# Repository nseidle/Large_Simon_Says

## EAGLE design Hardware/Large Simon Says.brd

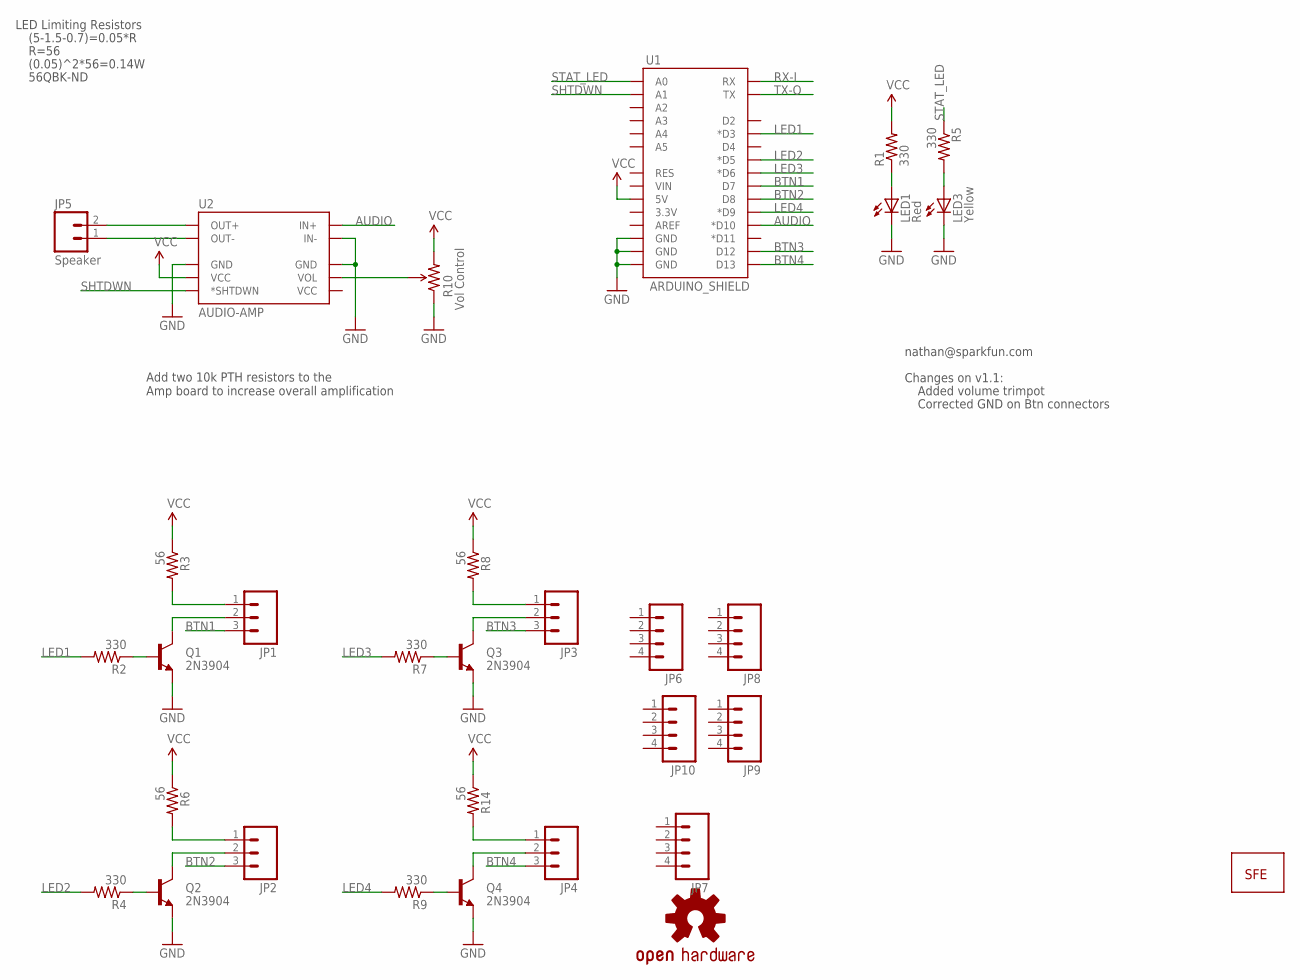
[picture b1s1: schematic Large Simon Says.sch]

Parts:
JP1, JP2, JP3, JP4: M03JST-PTH-VERT; JST-3-PTH-VERT
JP5: Speaker; JST-2-PTH
JP6, JP7, JP8, JP9, JP10: M04JST-PTH; JST-4-PTH
LED1: Red; LED5MM
LED3: Yellow; LED5MM
Q1, Q2, Q3, Q4: 2N3904; TO-92
R1, R2, R4, R5, R7, R9: 330; AXIAL-0.3
R3, R6, R8, R14: 56; AXIAL-0.3
R10: Vol Control; 3386U
U1: ARDUINO_SHIELD; DUEMILANOVE_SHIELD_NOHOLES
U2: AUDIO-AMP; AUDIO-AMP-MONO
U$1: LOGO-SFENEW; SFE-NEW-WEBLOGO
U$3: OSHW-LOGOS; OSHW-LOGO-S

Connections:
AUDIO: U1.D10 (*D10), U2.IN+
BTN1: JP1.3, U1.D7
BTN2: JP2.3, U1.D8
BTN3: JP3.3, U1.D12
BTN4: JP4.3, U1.D13
GND: LED1.K (C), LED3.K (C), Q1.1 (E), Q2.1 (E), Q3.1 (E), Q4.1 (E), R10.1 (CCW), U1.GND@0 (GND), U1.GND@1 (GND), U1.GND@2 (GND), U2.IN-, U2.PWR- (GND), U2.VOL- (GND)
LED1: R2.P$2 (2), U1.D3 (*D3)
LED2: R4.P$2 (2), U1.D5 (*D5)
LED3: R7.P$2 (2), U1.D6 (*D6)
LED4: R9.P$2 (2), U1.D9 (*D9)
unnamed: LED1.A, R1.P$1 (1)
unnamed: Q1.2 (B), R2.P$1 (1)
unnamed: JP1.2, Q1.3 (C)
unnamed: LED3.A, R5.P$2 (2)
unnamed: JP1.1, R3.P$2 (2)
unnamed: JP2.2, Q2.3 (C)
unnamed: JP4.2, Q4.3 (C)
unnamed: JP5.2, U2.OUT+
unnamed: Q2.2 (B), R4.P$1 (1)
unnamed: JP2.1, R6.P$2 (2)
unnamed: Q3.2 (B), R7.P$1 (1)
unnamed: Q4.2 (B), R9.P$1 (1)
unnamed: JP5.1, U2.OUT-
unnamed: R10.2 (WIPER), U2.VOL
unnamed: JP3.1, R8.P$2 (2)
unnamed: JP4.1, R14.P$2 (2)
unnamed: JP3.2, Q3.3 (C)
RX-I: U1.RX
SHTDWN: U1.A1, U2.S (*SHTDWN)
STAT_LED: R5.P$1 (1), U1.A0
TX-O: U1.TX
VCC: R1.P$2 (2), R3.P$1 (1), R6.P$1 (1), R8.P$1 (1), R10.3 (CW), R14.P$1 (1), U1.5V, U2.PWR+ (VCC)

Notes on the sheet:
Changes on v1.1:
nathan@sparkfun.com
LED Limiting Resistors
(5-1.5-0.7)=0.05*R
R=56
(0.05)^2*56=0.14W
56QBK-ND
Add two 10k PTH resistors to the Amp board to increase overall amplification
Added volume trimpot
Corrected GND on Btn connectors

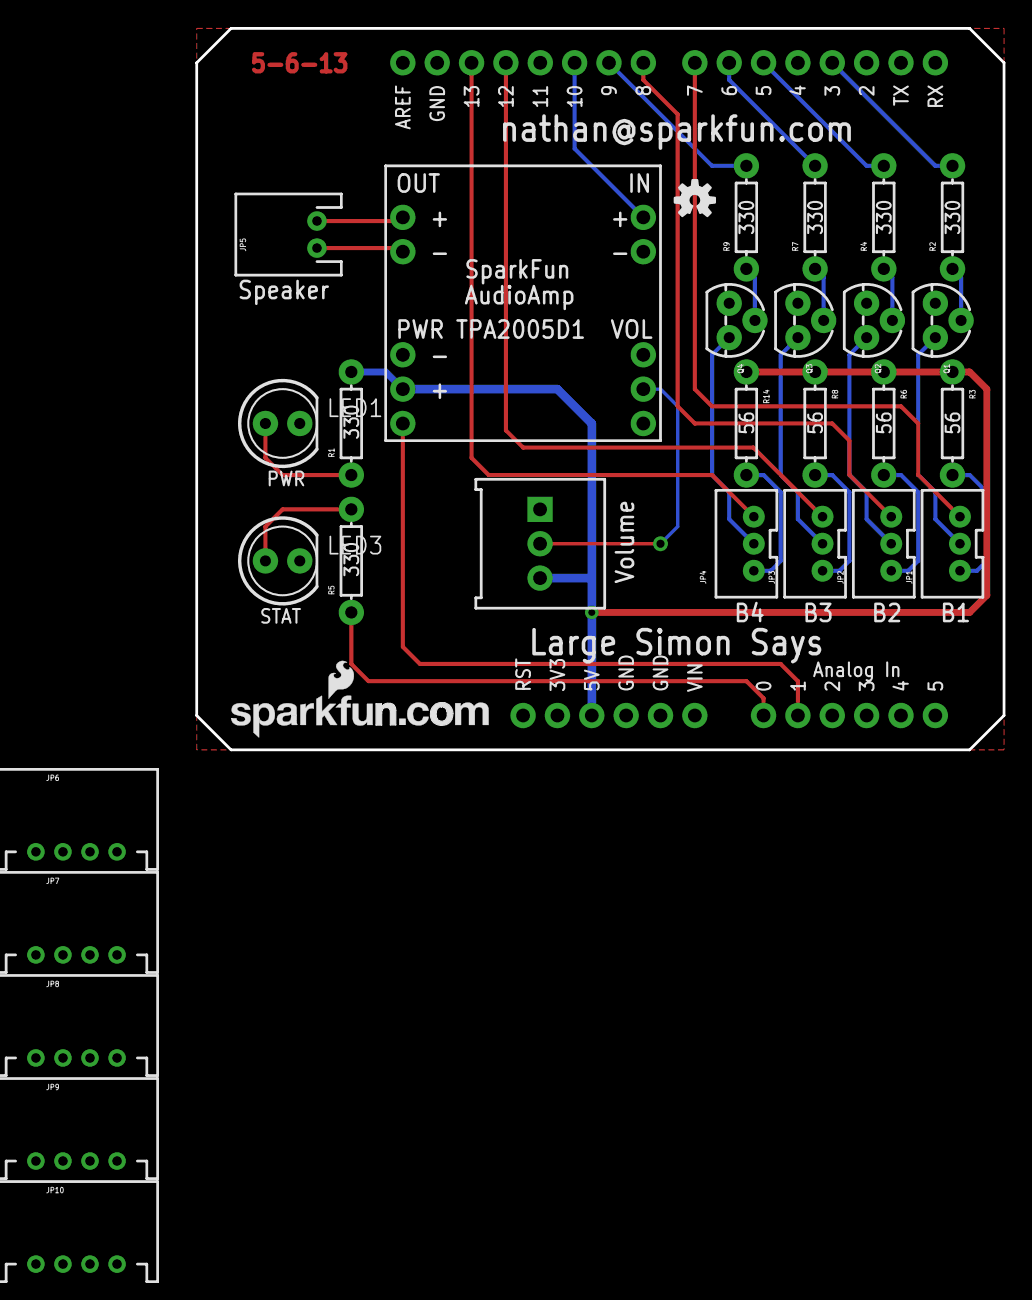
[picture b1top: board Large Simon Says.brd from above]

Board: 2 copper layers, 59.7 x 53.3 mm, 31 parts (0 on the bottom side), 30 nets.

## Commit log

2013-05-06 Updated .ignore and removed extra files.
2013-05-06 Removing version number
    This is considered v1.0.
2013-06-10 Adding firmware. Small changes to hardware.
    The button connectors are missing a ground connection. Thought I could
    do it with three, but it was a mistake.

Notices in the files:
parts and their libraries:
SparkFun-Boards: Licensing: CC v3.0 Share-Alike You are welcome to use this library for commercial purposes.
